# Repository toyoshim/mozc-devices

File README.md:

Circuit diagrams and firmware source code for Gboard DIY keyboards, previously
known as Google Japanese Input / Gboard April Fools.

This is not an officially supported Google product.

# Products

Please refer to the README in each directory for more details.

<table>
<tr>
<td>

[Google 日本語入力 ドラムセットバージョン](https://archive.google/drumsetkeyboard/)<br>
[Google Japanese Input Drum set version](https://archive.google/drumsetkeyboard/)

変換の煩わしさを感じさせない思いどおりの日本語入力を提供します。

- [Announce](https://blog.google/intl/ja-jp/products/android-chrome-play/2010_04_google/)
- Release date: Apr 1, 2010
- Source: Not open source

</td>
<td>

[Google 日本語入力 モールスバージョン](http://www.google.co.jp/ime/-.-.html)<br>
[Google Japanese Input Morse version](http://www.google.co.jp/ime/-.-.html)

モールス符号で思いどおりの日本語入力

- [Promotional video](https://www.youtube.com/watch?v=u5AYb778pwA)
- [Announce](https://japan.googleblog.com/2012/04/google.html)
- [Technical details](http://googledevjp.blogspot.jp/2012/06/google.html)
- Release date: Apr 1, 2012
- Source: [/third_party/mozc-morse](./third_party/mozc-morse)

</td>
</tr>
<tr>
<td>

[Google 日本語入力 パタパタバージョン](http://www.google.co.jp/ime/patapata/)<br>
[Google Japanese Input Patapata version](http://www.google.co.jp/ime/patapata/)

もう、なにも覚える必要はありません。
押して離すだけの日本語入力。

- [Promotional video](https://www.youtube.com/watch?v=HzUDAaYMNsA)
- [Announce](https://japan.googleblog.com/2013/04/google-patapata.html)
- [Technical details](http://googledevjp.blogspot.jp/2013/10/google.html)
- Release date: Apr 1, 2013
- Source: [/third_party/mozc-flap](./third_party/mozc-flap)

</td>
<td>

[Google 日本語入力 マジックハンドバージョン](https://archive.google/ime/m9/)<br>
[Google Japanese Input Magic hand version](https://archive.google/ime/m9/)

マジックハンドでらくらく入力

- [Promotional video](https://www.youtube.com/watch?v=0u1zoaJYAmw)
- [Announce](https://blog.google/intl/ja-jp/products/android-chrome-play/2014_04_m9/)
- Release date: Apr 1, 2014
- Source: Not open source

</td>
</tr>
<tr>
<td>

[Google 日本語入力 ピロピロバージョン](https://www.google.co.jp/ime/___o/)<br>
[Google Japanese Input Piropiro version](https://www.google.co.jp/ime/___o/)

もうキーはいらない

- [Promotional video](https://www.youtube.com/watch?v=gAgOnQqyDz0)
- [Announce](https://japan.googleblog.com/2015/04/piropiro.html)
- Release date: Apr 1, 2015
- Source: [/mozc-piropiro](./mozc-piropiro)

</td>
<td>

[Google 日本語入力 物理フリックバージョン](https://www.google.co.jp/ime/furikku/)<br>
[Google Japanese Input Physical Flick version](https://www.google.co.jp/ime/furikku/)

さわれるフリック

- [Promotional video](https://www.youtube.com/watch?v=5LI1PysAlkU)
- [Announce](https://japan.googleblog.com/2016/04/furikku.html)
- Release date: Apr 1, 2016
- Source: [/mozc-furikku](./mozc-furikku)

</td>
</tr>
<tr>
<td>

[日本語入力 プチプチバージョン](https://landing.google.co.jp/ime/ooooo/)<br>
[Google Japanese Input Puchi Puchi version](https://landing.google.co.jp/ime/ooooo/)

空気のように、軽やかな入力。

- [Promotional video](https://www.youtube.com/watch?v=RkJZDvHMyTA)
- [Announce](https://japan.googleblog.com/2017/04/ooooo.html)
- Release date: Apr 1, 2017
- Source: [/third_party/mozc-puchi](./third_party/mozc-puchi)

</td>
<td>

[Gboard 物理手書きバージョン](https://landing.google.co.jp/tegaki/)<br>
[Gboard Physical Handwriting version](https://landing.google.co.jp/tegaki/)

新しいタイプの手書き入力。

- [Promotional video](https://www.youtube.com/watch?v=guJnFY1R4I0)
- [Announce](https://japan.googleblog.com/2018/04/tegaki.html)
- [Technical details](https://developers-jp.googleblog.com/2018/04/tegaki.html)
- Release date: Apr 1, 2018
- Source: [/mozc-nazoru](./mozc-nazoru)

</td>
</tr>
<tr>
<td>

[Gboard スプーン曲げバージョン](https://landing.google.co.jp/---o/)<br>
[Gboard Spoon Bending version](https://landing.google.co.jp/---o/)

タネも仕掛けもない、柔軟な入力。

- [Promotional video](https://www.youtube.com/watch?v=DeJY5d14qKs)
- [Announce](https://japan.googleblog.com/2019/04/mageru.html)
- Release date: Apr 1, 2019
- Source:
  - [/mozc-mageru](./mozc-mageru) for firmware, schematics, and PCB layout.
  - [/third_party/mozc-mageru](./third_party/mozc-mageru) for 3D model.

</td>
<td>

[Gboard 湯呑みバージョン](https://g.co/yunomi/)<br>
[Gboard yunomi version](https://g.co/yunomi/)

もう、おすしかない。

- [Promotional video](https://www.youtube.com/watch?v=20pC05yisRM)
- [Announce](https://japan.googleblog.com/2021/10/gboard.html)
- Release date: Oct 1, 2021
- Source: [/mozc-yunomi](./mozc-yunomi)

</td>
</tr>
<tr>
<td>

[Gboard 棒バージョン](https://g.co/____)<br>
[Gboard bar version](https://g.co/____)

キーの次はボーです。

- [Promotional video](https://www.youtube.com/watch?v=9G3DWHf1xX0)
- [Announce](https://japan.googleblog.com/2022/10/gboard-2022.html)
- Release date: Oct 1, 2022
- Source: [/mozc-bar](./mozc-bar)

</td>
<td>

[Gboard 帽バージョン](https://g.co/CAPS)<br>
[Gboard CAPS version](https://g.co/CAPS)

入力は、帽険だ。

- [Promotional video](https://www.youtube.com/watch?v=6vib77CUxNM)
- [Announce](https://japan.googleblog.com/2023/10/caps.html)
- Release date: Oct 1, 2023
- Source: [/mozc-caps](./mozc-caps)

</td>
</tr>
<tr>
<td>

[Gboard 両面バージョン](https://g.co/double-sided)<br>
[Gboard double sided version](https://g.co/double-sided)

表面かと思ったら裏面でした。

- [Promotional video](https://www.youtube.com/watch?v=EHqPrHTN1dU)
- [Announce](https://blog.google/intl/ja-jp/products/android-chrome-play/gboard-2024)
- Release date: Oct 1, 2024
- Source: [/mozc-doublesided](./mozc-doublesided)

</td>
<td>

[Gboard ダイヤルバージョン](./mozc-dial/README_ja.md)<br>
[Gboard double sided version](./mozc-dial)

まるくおさめました。

- [Promotional video](https://youtu.be/BgdWyD0cBx4)
- [Announce](https://blog.google/intl/ja-jp/products/android-chrome-play/gboard-2025)
- Release date: Oct 1, 2025
- Source: [/mozc-dial](./mozc-dial)

</td>
</tr>
</table>

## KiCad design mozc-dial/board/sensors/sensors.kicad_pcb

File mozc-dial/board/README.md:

# Board Assembly Guide

For the entire keyboard assembly, please refer to the [Build Guide](../buildguide.md).

## Common to All Editions

### Sensor Board (per board)

#### Bill of Materials

| Ref | Description | Qty | Notes |
|---|---|---|---|
| R1,R3,R5 | Resistor 330Ω | 3 | Through-hole or surface-mount |
| R2,R4,R6 | Not populated | - | |
| U1-3 | Reflective photo sensor RPR-220 | 3 | (e.g., [Reflective Photo Sensor (Photoreflector) RPR-220](https://akizukidenshi.com/catalog/g/g111401/)) |
| J1 | 2.54mm pitch 1x5 pin header | 1 | L-shaped is desirable (e.g., [Pin Header (Male L-type) 1x40 (40P)](https://akizukidenshi.com/catalog/g/g101627/)) |

#### Assembly

This explanation covers the case where all 3 bits are populated. However, for the 9-dial edition, some sensors may only require 1 or 2 bits. In that case, populate only the required number of components from the top (U1). For details, follow the instructions for the 9-dial edition.

Also, before making everything, it is recommended to check if the Gray code plate values can be read properly to reduce rework in case of problems. If it doesn't work well, populate resistors on R2, R4, and R6. For details, see [Reading Sensor Adjustment](#reading-sensor-adjustment).

First, attach the photo sensors from the side where the U1, U2, and U3 markings are visible. Pay close attention to the orientation. The upper right corner is chamfered, so check the marking and the shape of the sensor to ensure they are in the same orientation. After correct placement, cut off the excess leads from the back and solder them.

On the back side, there are places to attach three resistors on the `(SENSOR)` side and three on the `(LED)` side, as shown in the figure. Both through-hole and chip resistors can be used, so use the parts of your choice. However, even for through-hole types, it is more stable to mount them without passing them through the holes when attaching the dial.

As mentioned earlier, the resistors depend on the adjustment, but it is recommended to leave the `(SENSOR)` side unpopulated and install 330Ω resistors on the `(LED)` side as a standard.

For the 1x5 pin header, using an L-shaped one will fit well in the case.

During assembly, pay attention to the `⇧Center` mark. The inner circumference of the dial will be in the direction of the arrow.

## 1-Dial Edition

This is an introductory edition that uses commercially available general-purpose parts other than the sensor board.

### Parts

- Raspberry Pi Pico: 1
- Sensor board (3-bit populated): 2
- [Unipolar Stepping Motor 28BYJ-48 5V](https://akizukidenshi.com/catalog/g/g113256/): 1
- [Stepping Motor Drive Module [M2003S]](https://www.aitendo.com/product/12366): 1
- Wiring materials: as needed

### Assembly

#### Sensor Board

Assemble two 3-bit populated sensor boards as described in the common section for all dial editions. We will call one `SENSOR L` and the other `SENSOR H`.

Although not a clean example as it was used for experiments, here are examples of mounting both through-hole and chip resistors.

Each board's pin header has five terminals: `V`, `1`, `2`, `3`, and `G`.
Of these, `V` connects to the 3.3V power supply, but the Raspberry Pi Pico we are using has only one 3.3V output terminal. Therefore, connect the terminal pair where `V` passes on the board, as shown by the red wiring in the photo.
In the diagram for the sensor board, the terminals inside the rectangle labeled `V`, that is, the six outer locations of the resistor patterns, are `V`.

The upper sensor board is `SENSOR L` for the inner circumference, and the lower sensor board is `SENSOR H` for the outer circumference.
Since `V` is interconnected, the `V` at the top-most, inner-most terminal is not needed for this connection.

#### Stepping Motor Drive Module

The Raspberry Pi Pico's GPIO cannot drive the motor directly, so the 1-dial edition uses a commercially available drive module. Any sink-type driver other than the one specified here will work, and you can also build your own by referring to the circuit of the 9-dial edition.

Taking the one mentioned here as an example, `IN1` to `IN4` enclosed in green are the terminals that receive the outputs `1` to `4` from the Raspberry Pi Pico. `GND` enclosed in black and `VCC` enclosed in red are `G` and `V` respectively.
The motor draws 5V power from the USB bus via the Raspberry Pi Pico. It requires about 0.3A, so the firmware for the 1-dial edition requests the 0.5A upper limit for USB micro.

The white terminal is used for connection with the stepping motor.

#### Raspberry Pi Pico

Attach L-shaped pin headers to a commercially available Raspberry Pi Pico as shown in the photo.
The three DEBUG pins at the bottom of the photo are optional and only needed if you need to develop and debug the firmware.

The pins used in the 1-dial edition are assigned as shown in the diagram. Connect to SENSOR L, SENSOR H, and MOTOR according to this diagram. When debugging, the standard output is output from TX via UART.

### Firmware Flashing

Follow the general method for the Raspberry Pi Pico. Connect the Raspberry Pi Pico to your PC while holding down the `BOOT` button on the board. A drive named `RPI-RP2` will appear. Copy `firmware/prebuilt/one_dial.uf2` into this drive. If the flashing is successful, the drive will disappear. Your OS may show a warning, but this is not a problem. From now on, when you connect this device to your PC without holding down the `BOOT` button, it will be recognized as a USB keyboard.

## 9-Dial Edition

### Parts

- Main board: 1
- Sensor board (3-bit populated): 6
- Sensor board (2-bit populated): 4
- Sensor board (1-bit populated): 1
- [Unipolar Stepping Motor 28BYJ-48 5V](https://akizukidenshi.com/catalog/g/g113256/): 9
- Wiring materials: as needed

### Main Board

#### Bill of Materials

| Ref | Description | Qty | Notes |
|---|---|---|---|
| C101 | Capacitor 10uF | 1 | |
| C102-121,C202-208,C212,C302-308,C312 | Capacitor 100nF | 36 | |
| C201,C209,C301,C309 | Capacitor 1uF | 4 | |
| C210,C211,C310,C311 | Capacitor 20pF | 4 | |
| J102-103 | 2.54mm pitch 1x3 pin header | 2 | |
| J106-J125 | 2.54mm pitch 1x5 pin header | 20 | |
| J201,J301 | USB TYPE C Receptacle | 2 | |
| R201-202,R301-302 | Resistor 27.4Ω | 4 | |
| R203-204,R303-304 | Resistor 5.1KΩ | 4 | |
| R205,R207,R305,R307 | Resistor 1KΩ | 4 | |
| R206,R306 | Resistor 10KΩ | 2 | |
| SW101,SW201,SW301 | Switch | 3 | |
| U101 | AMS1117 3.3V Regulator | 1 | |
| U102-103,U105,U107,U109 | TBD62083AFNG | 5 | |
| U104,U106,U108,U110 | 74HC238 | 4 | |
| U201,U301 | RP2040 | 2 | |
| U202,U302 | W25Q128JVS | 2 | |
| Y201,Y301 | 12MHz Crystal Oscillator | 2 | |
| N/A | Jumper pin | 2 | |

#### Assembly

Currently, we have released up to the schematics. We will release the Gerber data soon, so please look forward to it!

### Assembly

Attach 1x5 L-shaped pin headers for connecting to the sensor boards to `SENSOR A-L`, `SENSOR A-H`, `SENSOR B`, `SENSOR C`, `SENSOR D`, `SENSOR E`, `SENSOR F`, `SENSOR G`, `SENSOR H`, `SENSOR I-L`, and `SENSOR I-H`.

Attach 1x5 L-shaped pin headers for connecting to the motors to `MOTOR A`, `MOTOR B`, `MOTOR C`, `MOTOR D`, `MOTOR E`, `MOTOR F`, `MOTOR G`, `MOTOR H`, and `MOTOR I`.

Attach a 1x3 pin header to the location marked `U1 PWR U2` and short the `U1` and `PWR` positions with a jumper pin.

Attach a 1x3 pin header to the location marked `USB V_MTR ALT` and short the `USB` and `V_MTR` positions with a jumper pin.

### Sensor Board

Referring to the [Common to All Dial Editions](#common-to-all-dial-editions) section, prepare a total of 11 sensor boards with the following populated bit widths. There is no problem other than an increase in standby power consumption if you populate more bits, so it is also fine to prepare all of them with a 3-bit width.

| Ref | Populated Bit Width |
|---|---|
| SENSOR A-L | 3 |
| SENSOR A-H | 3 |
| SENSOR B | 2 |
| SENSOR C | 3 |
| SENSOR D | 2 |
| SENSOR E | 3 |
| SENSOR F | 3 |
| SENSOR G | 2 |
| SENSOR H | 2 |
| SENSOR I-L | 3 |
| SENSOR I-H | 1 |

## Photo Sensor Adjustment

The photo sensor readings should not vary greatly as they are taken inside the case, but differences may arise due to the brightness of the 3D printing material or the quality of the paper on which the Gray code is printed. If the dial reading is unstable or the rotation does not stop, the sensor value change range may not be within the expected range. In that case, please adjust the sensor paying attention to the following points.

### Reading with RP2040

The sensor value is processed as a digital value by GPIO. Therefore, it needs to be adjusted so that HIGH is in the range of 2.0 - 3.3[V] and LOW is in the range of 0.0 - 0.3[V] when operating at 3.3V.

### LED Sensor Adjustment

If the current flowing through the LED is small, the light emission will be weak, and the amount of light read by the sensor will be insufficient. This will result in higher readings, and the voltage difference between white and black will not be clear. In that case, try changing the three resistors on the `(LED)` side to weaker ones. The standard is adjusted with 330Ω, but with the photo sensor RPR-220 used this time, it will stay within the rated value even if you lower it to about 40Ω. However, it will greatly affect the standby power consumption, so if possible, please adjust with the resistor on the reading sensor side.

### Reading Sensor Adjustment

You can shift the read voltage value by changing the pull-up resistance of the reading sensor. However, if you change it too much, the voltage difference between white and black will become less clear. You can adjust it by populating the three resistors on the `(SENSOR)` side. The standard firmware expects a pull-up of about 50-80KΩ by the RP2040's pull-up. If the voltage does not rise sufficiently with black, it is better to pull-up more strongly with an additional resistor. By following the [Firmware Development Guide](../firmware/README.md) and disabling the RP2040's pull-up, the resistor populated here will become the pull-up resistor. If you do not disable it, it will be pulled up by the combined resistance in parallel. The calculation is a bit complicated, but it may be easier to pull-up in parallel with an additional resistor without changing the firmware if you want to pull-up more strongly.

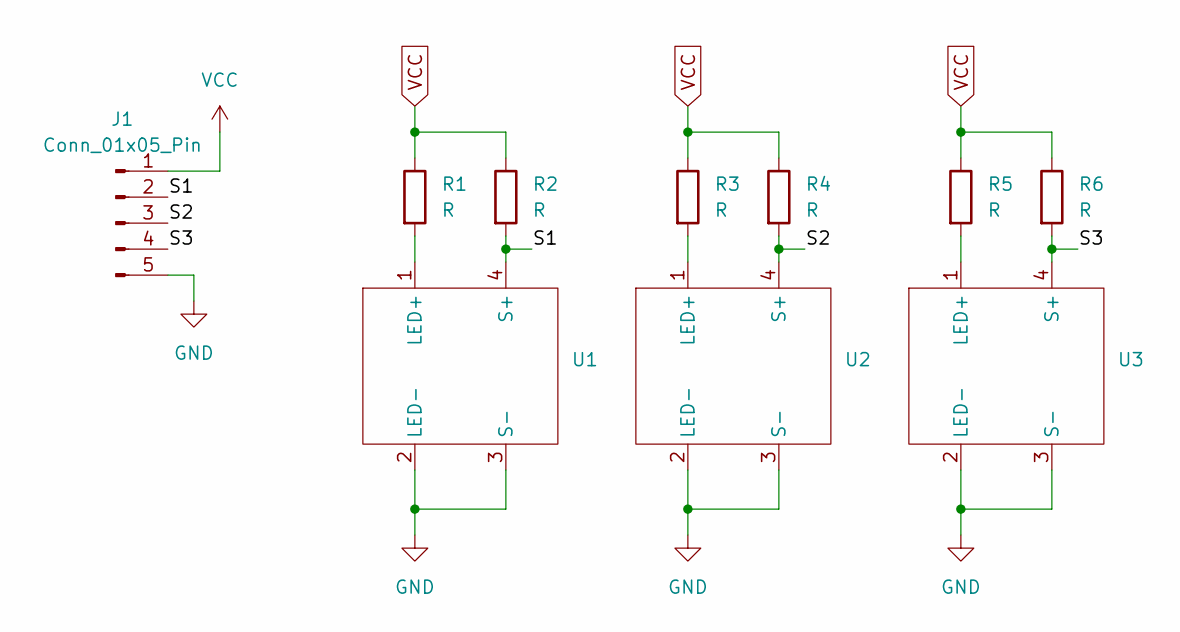
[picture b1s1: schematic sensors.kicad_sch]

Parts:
J1: Conn_01x05_Pin; PinHeader_1x05_P2.54mm_Vertical
R1, R2, R3, R4, R5, R6: R; Registor
U1, U2, U3: RPR220

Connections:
/S1: J1.2, R2.2, U1.4 (S+)
/S2: J1.3, R4.2, U2.4 (S+)
/S3: J1.4, R6.2, U3.4 (S+)
GND: J1.5, U1.2 (LED-), U1.3 (S-), U2.2 (LED-), U2.3 (S-), U3.2 (LED-), U3.3 (S-)
unnamed: R1.2, U1.1 (LED+)
unnamed: R3.2, U2.1 (LED+)
unnamed: R5.2, U3.1 (LED+)
VCC: J1.1, R1.1, R2.1, R3.1, R4.1, R5.1, R6.1

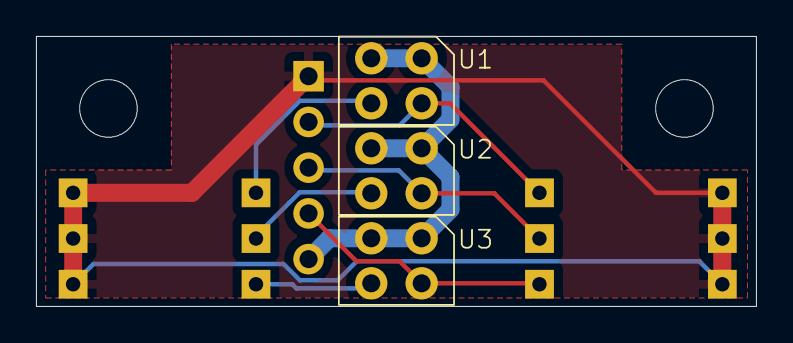
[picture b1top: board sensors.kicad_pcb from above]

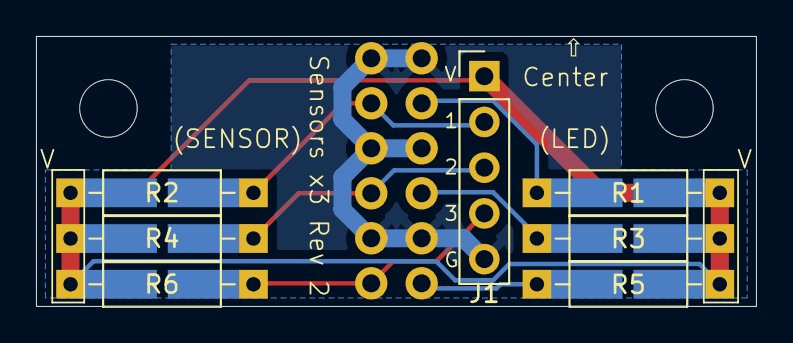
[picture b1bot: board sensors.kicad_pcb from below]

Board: 2 copper layers, 40.0 x 15.0 mm, 12 parts (7 on the bottom side), 8 nets.

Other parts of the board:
REF1, REF2: MountingHole_3.2mm_M3

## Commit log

2025-10-01 Add mozc dial version.
